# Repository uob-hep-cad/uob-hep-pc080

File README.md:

# uob-hep-pc080

Test board to break out every pin on SFP - for use with DUNE timing system QC

Manufacturing files for the SFP plug part ( to be used with SFP case recovered from TE 2127931-3 DAC ) are in a [zip archive](hardware/KiCAD/Manufacturing/pc080_sfp_plug_29sept26.zip)

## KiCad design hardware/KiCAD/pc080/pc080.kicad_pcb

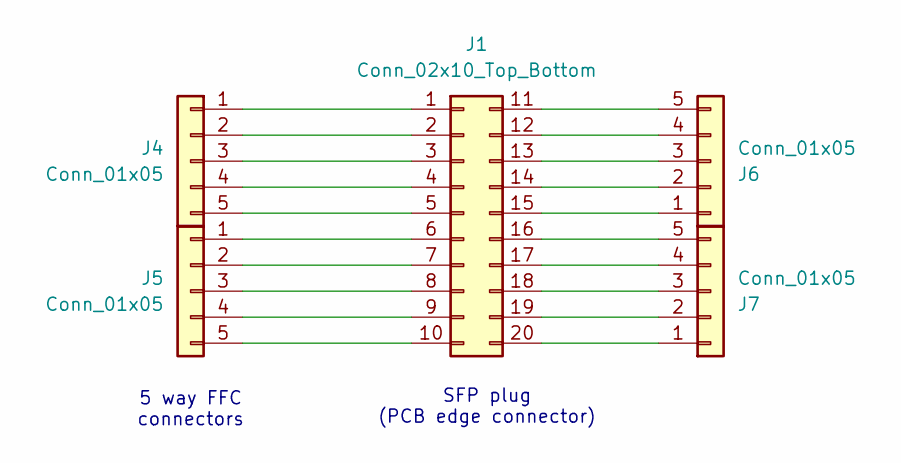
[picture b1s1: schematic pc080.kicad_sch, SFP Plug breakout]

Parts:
J1: Conn_02x10_Top_Bottom; SFP_Plug
J4, J5, J6, J7: Conn_01x05; AMPHENOL_59453-051110ECHLF

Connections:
unnamed: J1.1, J4.1
unnamed: J1.2, J4.2
unnamed: J1.3, J4.3
unnamed: J1.4, J4.4
unnamed: J1.5, J4.5
unnamed: J1.6, J5.1
unnamed: J1.7, J5.2
unnamed: J1.8, J5.3
unnamed: J1.9, J5.4
unnamed: J1.10, J5.5
unnamed: J1.11, J6.5
unnamed: J1.12, J6.4
unnamed: J1.13, J6.3
unnamed: J1.14, J6.2
unnamed: J1.15, J6.1
unnamed: J1.16, J7.5
unnamed: J1.17, J7.4
unnamed: J1.18, J7.3
unnamed: J1.19, J7.2
unnamed: J1.20, J7.1

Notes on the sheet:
SFP plug (PCB edge connector)
5 way FFC connectors

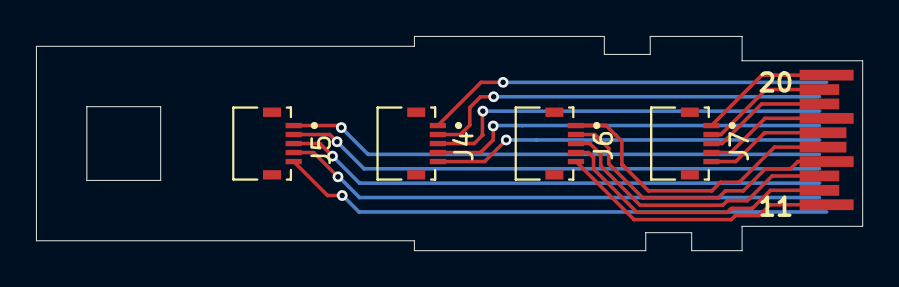
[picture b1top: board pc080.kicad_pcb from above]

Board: 2 copper layers, 45.9 x 11.9 mm, 5 parts (0 on the bottom side), 20 nets.

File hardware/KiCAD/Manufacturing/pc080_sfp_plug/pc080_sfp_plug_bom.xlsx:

Id | Designator | Footprint | Quantity | Designation | Manufacturer | Manufacturer part | Supplier | Supplier code
1 | J4, J5, J6, J7 | AMPHENOL_59453-051110ECHLF | 4 | Conn_01x05 | Amphenol | 59453-051110ECHLF | Farnell | 3911255
